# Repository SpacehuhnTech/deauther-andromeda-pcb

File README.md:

# Deauther Andromeda PCB
----------
<a href="https://spacehuhn.store/product/deauther-andromeda/"><br/>
Click here to purchase one from the shop</a>

PCB files for the Deauther andromeda.

Format is KiCad project.
KiCad version 5.1.4 is used during developmen prosess.

### Description
A small but powerfull board. this board is made to make full use of the wifi deauther. The serial connection is to be used for a powerfull and precise control of the deauther software.
This paired with the SMA connector, gives you the freedom to go as small and covert as you want. but you can also go big and bold. Tis power at your finger tips, just by a small and simpel extra.

A USB-powered WiFi pentesting tool based on the ESP8266.
Optimized for the [ESP8266 Deauther V3](https://github.com/SpacehuhnTech/esp8266_deauther/tree/v3) and [Huhnitor](https://github.com/spacehuhntech/huhnitor).  

Hardware features include:  
* SMA antenna connector
* USB-A plug
* ESP8266 WROOM 4MB Module
* FTDI serial chip

[Watch our video about the making-of:](https://www.youtube.com/watch?v=-opemq-5bIY)  

## Format

Made with [KiCad](https://kicad.org/) version 5.1.4

## Firmware

[ESP8266 Deauther](https://github.com/SpacehuhnTech/esp8266_deauther)

## License

This hardware design is published under CERN Open Hardware Licence Version 2 - Permissive, see the [license file](LICENSE) for details.

Designed by [Gerjon Eilander](https://github.com/13r1ckz) for Spacehuhn Technologies.

[Spacehuhn Technologies](https://spacehuhn.tech) invests time and resources providing this open source design, please consider supporting us by purchasing from [our store](https://spacehuhn.store).

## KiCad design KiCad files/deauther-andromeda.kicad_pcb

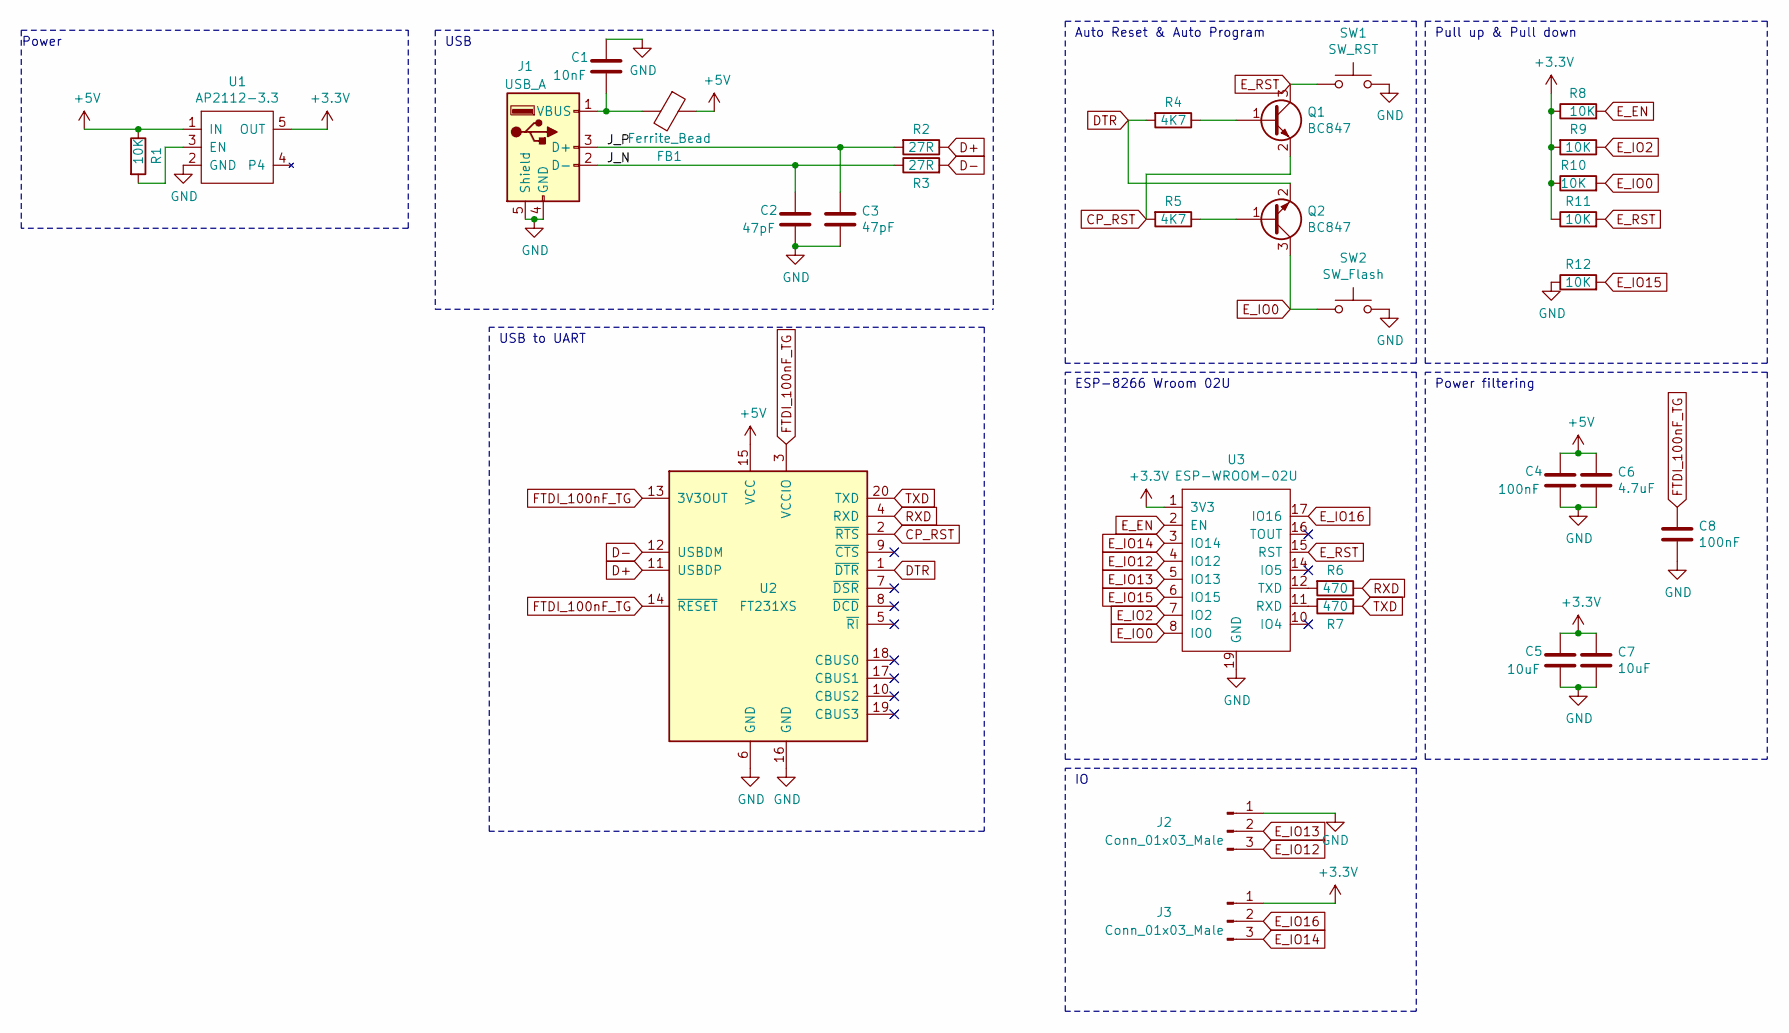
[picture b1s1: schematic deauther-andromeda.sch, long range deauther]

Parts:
C1: 10nF; C_0805_2012Metric_Pad1.15x1.40mm_HandSolder
C2, C3: 47pF; C_0805_2012Metric_Pad1.15x1.40mm_HandSolder
C4, C8: 100nF; C_0805_2012Metric_Pad1.15x1.40mm_HandSolder
C5, C7: 10uF; C_0805_2012Metric_Pad1.15x1.40mm_HandSolder
C6: 4.7uF; C_0805_2012Metric_Pad1.15x1.40mm_HandSolder
FB1: Ferrite_Bead; C_0805_2012Metric_Pad1.15x1.40mm_HandSolder
J1: USB_A; USB_A_CNCTech_1001-011-01101_Horizontal
J2, J3: Conn_01x03_Male; PinHeader_1x03_P2.54mm_Vertical
Q1, Q2: BC847; SOT-23
R1, R8, R9, R10, R11, R12: 10K; R_0805_2012Metric_Pad1.15x1.40mm_HandSolder
R2, R3: 27R; R_0805_2012Metric_Pad1.15x1.40mm_HandSolder
R4, R5: 4K7; R_0805_2012Metric_Pad1.15x1.40mm_HandSolder
R6, R7: 470; R_0805_2012Metric_Pad1.15x1.40mm_HandSolder
SW1: SW_RST; HYP_1TS003B-1600-3500A-CT
SW2: SW_Flash; HYP_1TS003B-1600-3500A-CT
U1: AP2112-3.3; AP2112_REGULATOR
U2: FT231XS; SSOP-20_3.9x8.7mm_P0.635mm
U3: ESP-WROOM-02U

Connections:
+3V3: C5.1, C7.1, J3.1, R8.1, R9.2, R10.1, R11.1, U1.5 (OUT), U3.1 (3V3)
+5V: C4.1, C6.1, FB1.1, R1.1, U1.1 (IN), U2.15 (VCC)
/J_N: C2.2, J1.2 (D-), R3.1
/J_P: C3.1, J1.3 (D+), R2.2
CP_RST: Q1.2 (E), R5.2, U2.2 (~RTS)
D+: R2.1, U2.11 (USBDP)
D-: R3.2, U2.12 (USBDM)
DTR: Q2.2 (E), R4.2, U2.1 (~DTR)
E_EN: R8.2, U3.2 (EN)
E_IO0: Q2.3 (C), R10.2, SW2.1, U3.8 (IO0)
E_IO2: R9.1, U3.7 (IO2)
E_IO12: J2.3, U3.4 (IO12)
E_IO13: J2.2, U3.5 (IO13)
E_IO14: J3.3, U3.3 (IO14)
E_IO15: R12.2, U3.6 (IO15)
E_IO16: J3.2, U3.17 (IO16)
E_RST: Q1.3 (C), R11.2, SW1.1, U3.15 (RST)
FTDI_100nF_TG: C8.1, U2.3 (VCCIO), U2.13 (3V3OUT), U2.14 (~RESET)
GND: C1.2, C2.1, C3.2, C4.2, C5.2, C6.2, C7.2, C8.2, J1.4 (GND), J1.5 (Shield), J2.1, R12.1, SW1.2, SW2.2, U1.2 (GND), U2.6 (GND), U2.16 (GND), U3.9 (GND), U3.13 (GND), U3.18 (GND), U3.19 (GND)
unnamed: C1.1, FB1.2, J1.1 (VBUS)
unnamed: Q1.1 (B), R4.1
unnamed: Q2.1 (B), R5.1
unnamed: R1.2, U1.3 (EN)
unnamed: R6.2, U3.12 (TXD)
unnamed: R7.1, U3.11 (RXD)
RXD: R6.1, U2.4 (RXD)
TXD: R7.2, U2.20 (TXD)

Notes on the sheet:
Power
USB
USB to UART
Auto Reset & Auto Program
Pull up & Pull down
ESP-8266 Wroom 02U
Power filtering

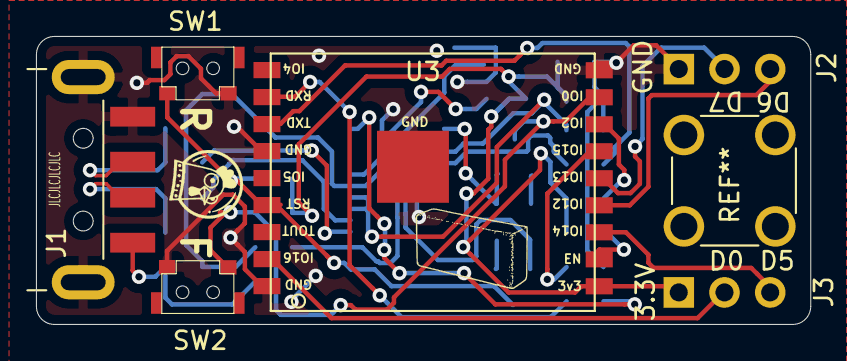
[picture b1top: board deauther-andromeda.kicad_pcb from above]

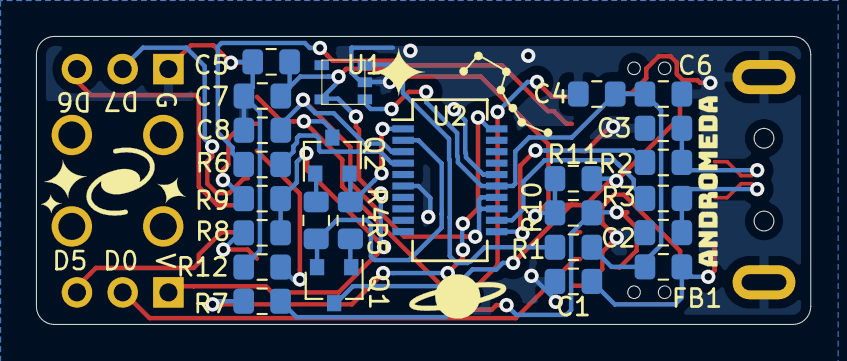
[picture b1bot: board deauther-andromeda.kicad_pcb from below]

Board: 2 copper layers, 43.0 x 16.0 mm, 31 parts (25 on the bottom side), 27 nets.

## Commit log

2020-10-02 next update with some update on pcb
    these updates are for use and for production.
    Changes are quickly listed in the changes.txt
2020-10-04 fixed idiote trace mistake
2020-10-04 updated the gerbers .zip
2020-10-04 Andromeda idiot fix (#2)
    * fixed idiote trace mistake
    * updated the gerbers .zip
2020-10-04 Add artwork on to pcb
2020-10-05 Will need to verify if these are right and if kicad has some issue with github or something. when opening the file after a day or after a git action some copper traces apear to change.
2020-10-19 inbetween push to pull on linux
2020-11-01 Def board version
2021-02-21 Long Needed git maintenance
2021-02-22 Update readme image
2021-02-22 Noting to see here just a document update
2021-03-01 manufactoring update
2021-03-01 fabrication commits 2 add fidus to pannel
2021-03-01 other production update
2021-03-01 other production stuff
2021-11-10 Update README.md
    https://forum.kicad.info/t/warning-avoid-all-links-to-kicad-pcb-org-use-kicad-org/31521
